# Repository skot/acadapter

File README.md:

# AC Infinity Fan Adapter

This project is a small KiCad adapter board for controlling an AC Infinity Cloudline fan from a controller fan header that provides an open-drain PWM output.

The current design is aimed at controllers such as Antminer and Bitaxe boards. The adapter translates the controller-side PWM signal into the Cloudline UIS PWM input without exposing the controller PWM node to the fan's internal 10 V pull-up.

## Project files

- `acadapter.kicad_pro`: KiCad project file
- `acadapter.kicad_sch`: schematic
- `acadapter.kicad_pcb`: PCB layout
- `doc/acinfinity-usbc.md`: Cloudline connector pinout and interface notes
- `doc/render.png`: PCB render

## Design summary

The Cloudline fan uses a proprietary UIS connector on USB-C pins. Based on measurement so far:

- Cloudline PWM is pulled up internally to +10 V through about 10 kOhm
- direct connection to an unknown controller PWM output is not assumed safe
- the adapter uses the Cloudline +10 V rail to generate a local +5 V rail
- a two-transistor buffer recreates an open-drain PWM output for the fan side

The current design note and rationale are documented in `doc/acinfinity-usbc.md`.

## Status

This is an in-progress hardware project. The PCB and interface notes are in the repository, but the design assumptions should still be validated against real hardware before treating the board as production-ready.

## License

This project is licensed under the CERN Open Hardware Licence Version 2 - Strongly Reciprocal (CERN-OHL-S v2).

See the `LICENSE` file for the full license text.

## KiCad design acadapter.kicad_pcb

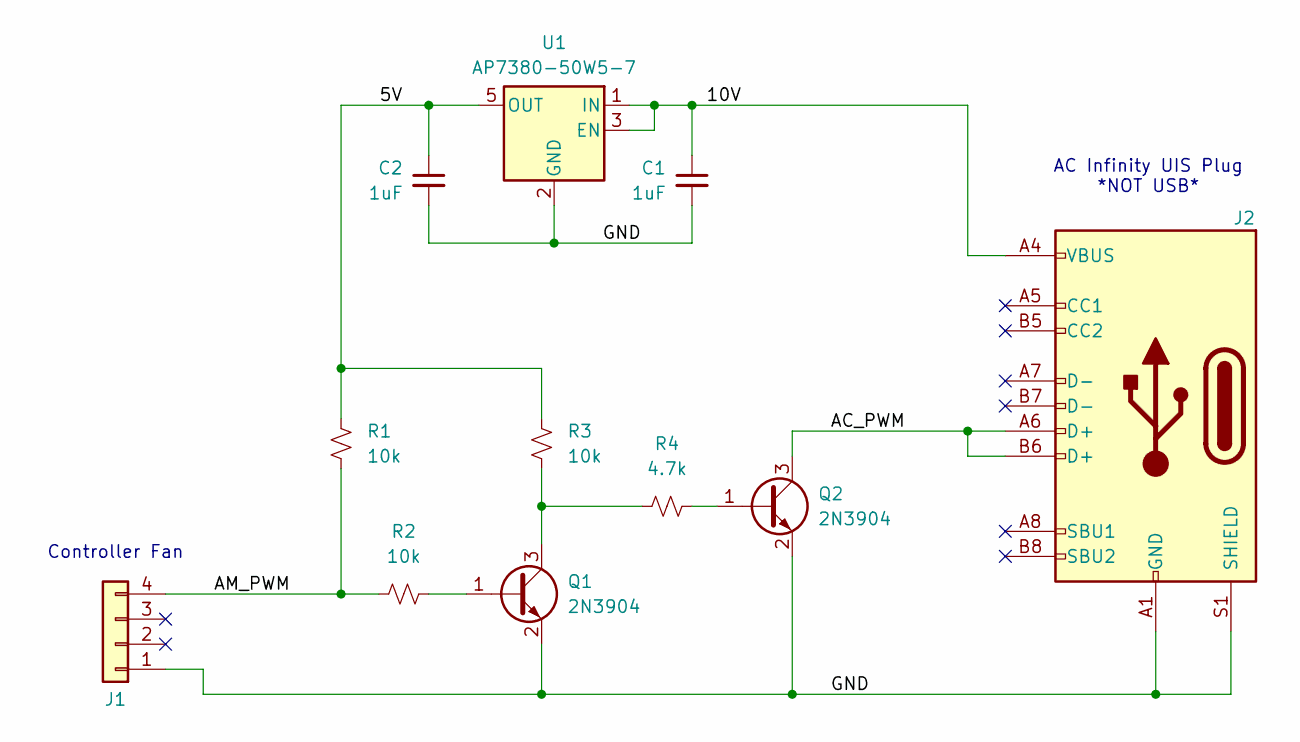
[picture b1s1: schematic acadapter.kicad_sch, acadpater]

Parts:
C1, C2: 1uF; C_0402_1005Metric; PARTNO GRM155C81E105KE11D
J1: Conn_01x04; PinSocket_1x04_P2.54mm_Horizontal; PARTNO 2042-1X04G00RB
J2: USB_C_Receptacle_USB2.0; USB_C_Receptacle_GCT_USB4105-xx-A_16P_TopMnt_Horizontal; LCSC C2988369
Q1, Q2: 2N3904; SOT-23; PARTNO MMBT3904-TP
R1, R2, R3: 10k; R_0402_1005Metric; PARTNO RC0402JR-0710KL
R4: 4.7k; R_0402_1005Metric; PARTNO RC0402FR-074K7L
U1: AP7380-50W5-7; SOT-23-5; PARTNO AP7380-50W5-7

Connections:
/5V: C2.1, R1.1, R3.1, U1.5 (OUT)
/10V: C1.1, J2.A4 (VBUS), J2.A9 (VBUS), J2.B4 (VBUS), J2.B9 (VBUS), U1.1 (IN), U1.3 (EN)
/AC_PWM: J2.A6 (D+), J2.B6 (D+), Q2.3 (C)
/AM_PWM: J1.4, R1.2, R2.1
/GND: C1.2, C2.2, J1.1, J2.A1 (GND), J2.A12 (GND), J2.B1 (GND), J2.B12 (GND), J2.S1 (SHIELD), Q1.2 (E), Q2.2 (E), U1.2 (GND)
unnamed: Q1.1 (B), R2.2
unnamed: Q1.3 (C), R3.2, R4.1
unnamed: Q2.1 (B), R4.2

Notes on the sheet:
Controller Fan
AC Infinity UIS Plug *NOT USB*

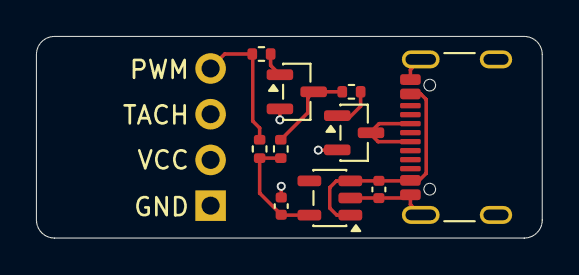
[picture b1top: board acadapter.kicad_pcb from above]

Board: 2 copper layers, 28.1 x 11.2 mm, 11 parts (1 on the bottom side), 8 nets.

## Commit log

2026-03-13 Add CERN Open Hardware Licence
    Added CERN Open Hardware Licence Version 2 - Strongly Reciprocal to the project.
2026-03-13 add license to readme. update part numbers
